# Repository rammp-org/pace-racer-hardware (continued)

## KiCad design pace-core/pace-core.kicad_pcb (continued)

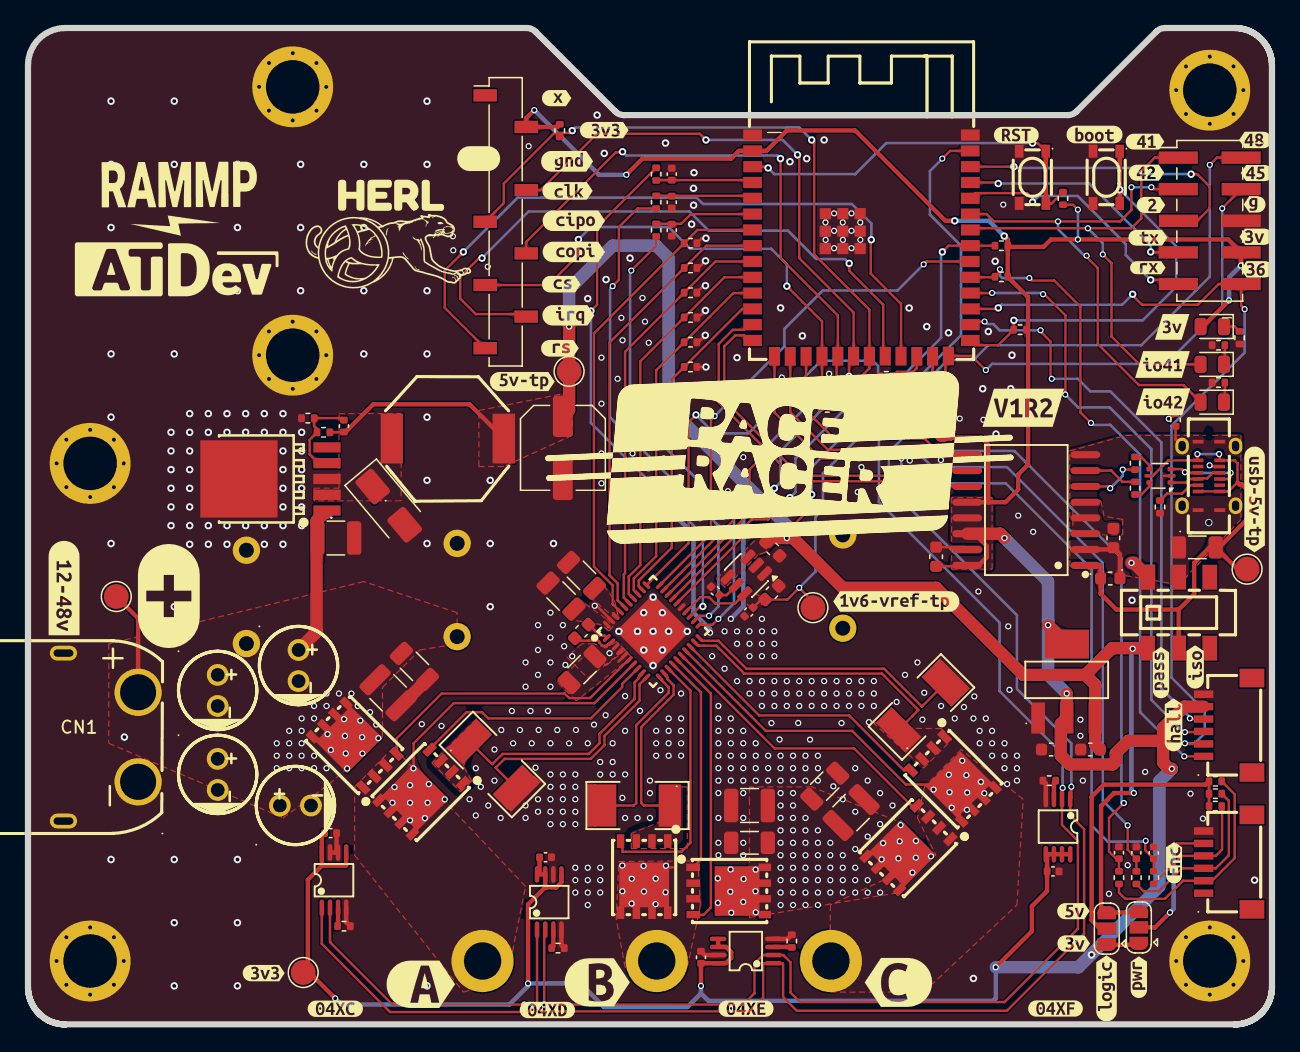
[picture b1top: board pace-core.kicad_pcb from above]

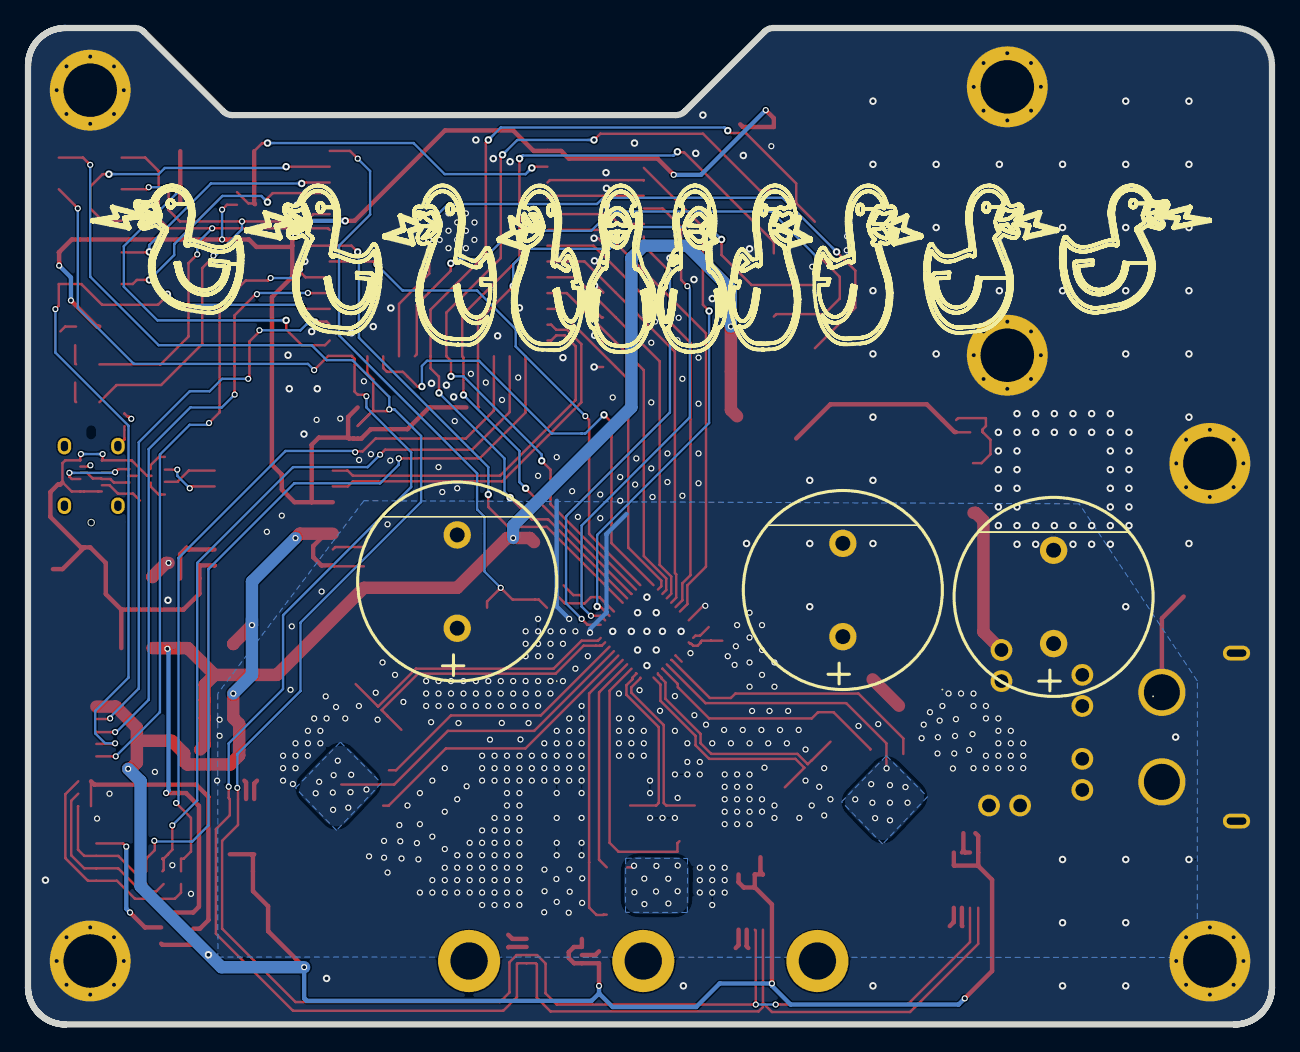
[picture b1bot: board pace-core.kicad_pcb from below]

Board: 4 copper layers, 100.0 x 80.1 mm, 175 parts (7 on the bottom side), 90 nets.

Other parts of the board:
kibuzzard-6A7D445B: G***; kibuzzard-6A7D445B
kibuzzard-6A7D4481: G***; kibuzzard-6A7D4481
kibuzzard-6A76A5A9: G***; kibuzzard-6A76A5A9
kibuzzard-6A76A5E2: G***; kibuzzard-6A76A5E2
kibuzzard-6A76A5F0: G***; kibuzzard-6A76A5F0
kibuzzard-6A76A7BD: G***; kibuzzard-6A76A7BD
kibuzzard-6A76A7CE: G***; kibuzzard-6A76A7CE
kibuzzard-6A76A8BC: G***; kibuzzard-6A76A8BC
kibuzzard-6A76A9E7: G***; kibuzzard-6A76A9E7
kibuzzard-6A76A71C: G***; kibuzzard-6A76A71C
kibuzzard-6A76A80F: G***; kibuzzard-6A76A80F
kibuzzard-6A76A83C: G***; kibuzzard-6A76A83C
kibuzzard-6A76A86B: G***; kibuzzard-6A76A86B
kibuzzard-6A76A548: G***; kibuzzard-6A76A548
kibuzzard-6A76A790: G***; kibuzzard-6A76A790
kibuzzard-6A76A802: G***; kibuzzard-6A76A802
kibuzzard-6A76A904: G***; kibuzzard-6A76A904
kibuzzard-6A76A908: G***; kibuzzard-6A76A908
kibuzzard-6A76A991: G***; kibuzzard-6A76A991
kibuzzard-6A76AA0A: G***; kibuzzard-6A76AA0A
kibuzzard-6A76AA3B: G***; kibuzzard-6A76AA3B
kibuzzard-6A76AAA5: G***; kibuzzard-6A76AAA5
kibuzzard-6A76AAC0: G***; kibuzzard-6A76AAC0
kibuzzard-6A76AAE1: G***; kibuzzard-6A76AAE1
kibuzzard-6A76AB0C: G***; kibuzzard-6A76AB0C
kibuzzard-6A76AB7D: G***; kibuzzard-6A76AB7D
kibuzzard-6A76AB8B: G***; kibuzzard-6A76AB8B
kibuzzard-6A76AB97: G***; kibuzzard-6A76AB97
kibuzzard-6A76ABC4: G***; kibuzzard-6A76ABC4
kibuzzard-6A76AD5A: G***; kibuzzard-6A76AD5A
kibuzzard-6A76AD71: G***; kibuzzard-6A76AD71
kibuzzard-6A793D41: G***; kibuzzard-6A793D41
kibuzzard-6A1928DD: G***; kibuzzard-6A1928DD
kibuzzard-6A1931C8: G***; kibuzzard-6A1931C8
kibuzzard-6A1931CD: G***; kibuzzard-6A1931CD
kibuzzard-6A1931D7: G***; kibuzzard-6A1931D7
kibuzzard-6A1931DC: G***; kibuzzard-6A1931DC
kibuzzard-6A1931E2: G***; kibuzzard-6A1931E2
kibuzzard-6A1931EE: G***; kibuzzard-6A1931EE
kibuzzard-6A79703A: G***; kibuzzard-6A79703A
kibuzzard-6A192903: G***; kibuzzard-6A192903
kibuzzard-6A192914: G***; kibuzzard-6A192914
kibuzzard-6A193405: G***; kibuzzard-6A193405
kibuzzard-6A193411: G***; kibuzzard-6A193411
kibuzzard-6A193434: G***; kibuzzard-6A193434
kibuzzard-6A769215: G***; kibuzzard-6A769215
kibuzzard-6A797050: G***; kibuzzard-6A797050

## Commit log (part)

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2026-06-03 manufacturing pcba order submitted
2026-06-04 Add documentation and resources section to README
    Added a section for documentation and resources with a link.
2026-06-04 Enhance README with project image
    Added an image to the README for better visual context.
2026-06-04 Enhance README with detailed hardware and firmware info
    Expanded documentation for the PACE V0 motor controller board, including hardware architecture, pin mapping, power distribution, and firmware initialization guidelines.
2026-06-04 Improve README content and structure
    Updated README to enhance documentation and formatting.
2026-06-04 Add new banner image to README
    Updated README to include new banner image.
2026-06-04 Enhance README with interactive board viewer link
    Updated the README to include a link with an image for accessing the interactive KiCanvas board viewer and schematics.
2026-06-04 Update image in README and clean up formatting
2026-06-04 updated shematic with test point image
2026-06-05 added kibot minimal workflow
2026-06-05 update for kicad 10 instead of 9
2026-06-05 tidy up
2026-06-05 update git workflows cicd
